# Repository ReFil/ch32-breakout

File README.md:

# ch32-breakout
 A Small ch32 breakout board complete with octagons

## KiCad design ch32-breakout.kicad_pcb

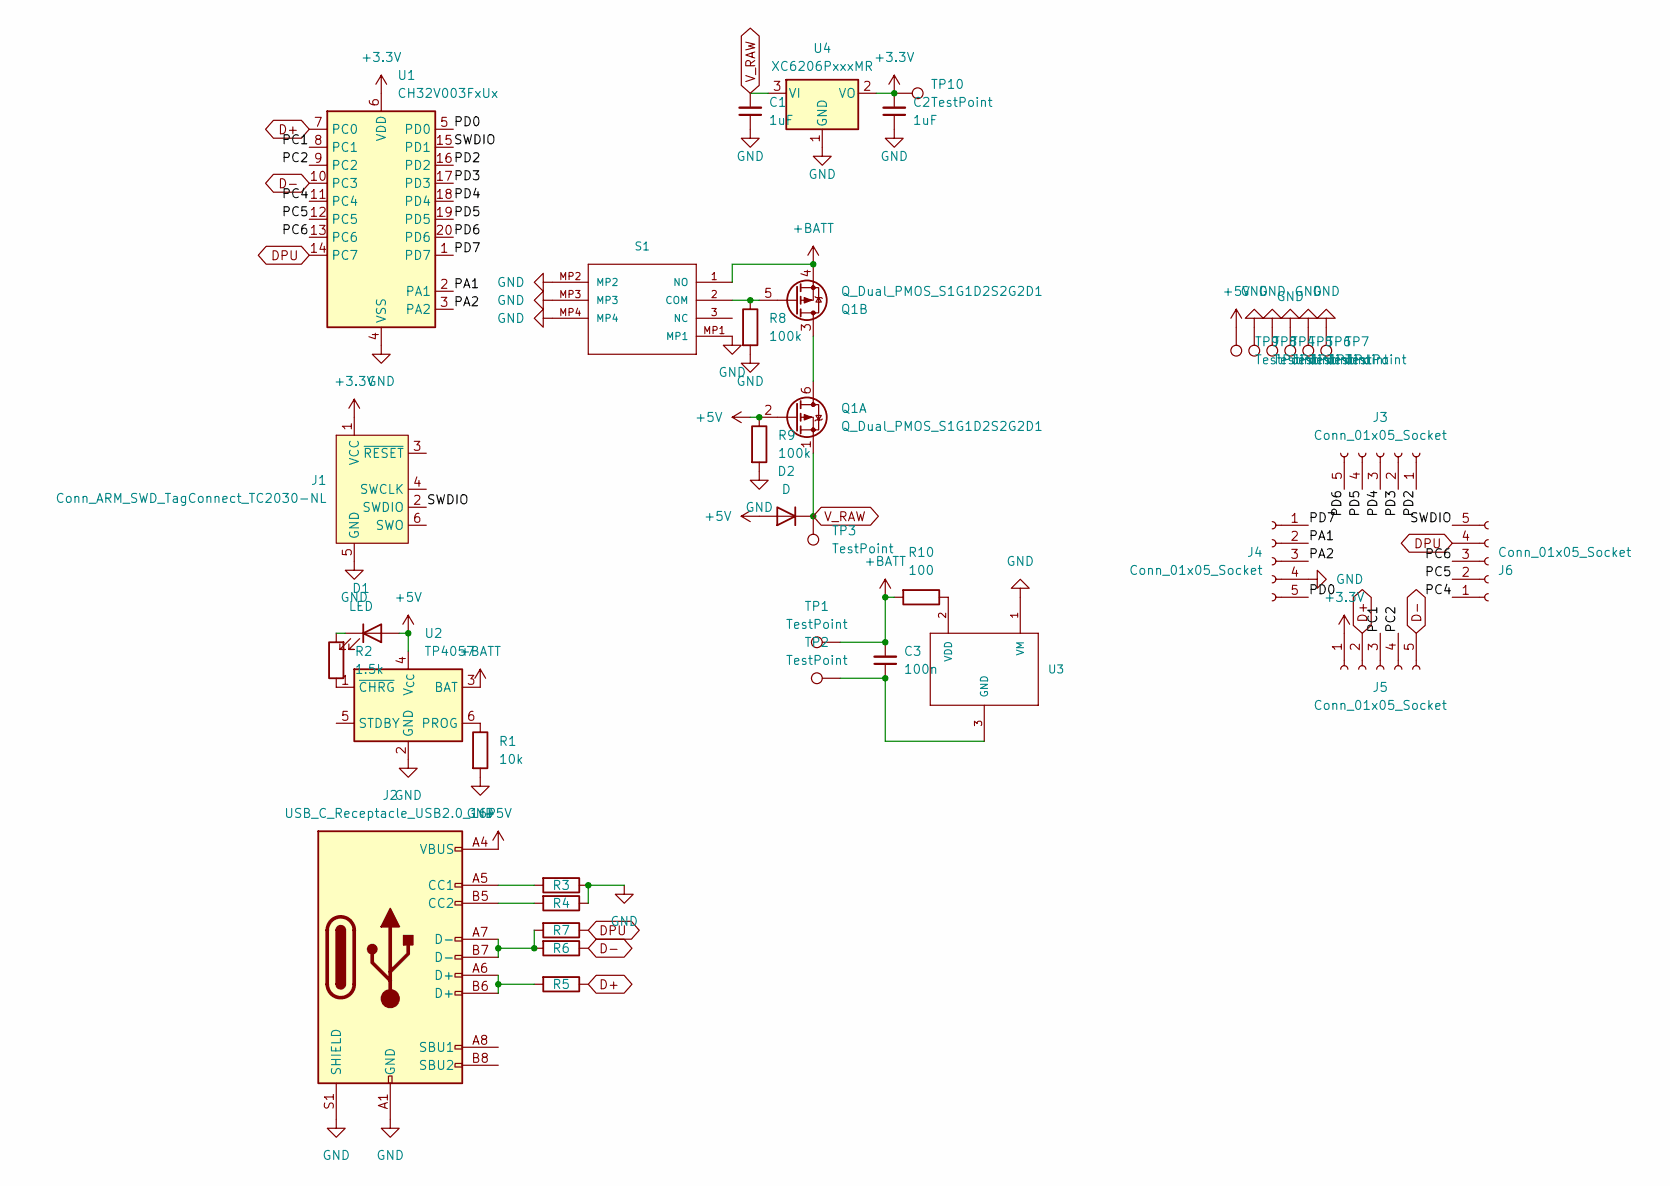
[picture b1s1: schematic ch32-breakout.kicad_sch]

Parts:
C1, C2: 1uF; C_0402_1005Metric; LCSC Part Number C2169363
C3: 100n; C_0402_1005Metric; LCSC Part Number C2169363
D1: LED; LED_0402_1005Metric; LCSC Part C5336761
D2: D; D_0603_1608Metric; LCSC Part C3758192
J1: Conn_ARM_SWD_TagConnect_TC2030-NL; Tag-Connect_TC2030-IDC-NL_2x03_P1.27mm_Vertical
J2: USB_C_Receptacle_USB2.0_16P; USB_C_Receptacle_XKB_U262-16XN-4BVC11; LCSC Part C319148
J3, J4, J5, J6: Conn_01x05_Socket; PinHeader_1x05_P1.27mm_Vertical_SMD_Pin1Left
Q1: Q_Dual_PMOS_S1G1D2S2G2D1; SOT-563; LCSC Part C504144
R1: 10k; R_0402_1005Metric; LCSC Part C60490
R2, R7: 1.5k; R_0402_1005Metric; LCSC Part C2929900
R3, R4: 5.1k; R_0402_1005Metric; LCSC Part C103086
R5, R6: 47; R_0402_1005Metric; LCSC Part C137973
R8, R9: 100k; R_0402_1005Metric; LCSC Part C2906883
R10: 100; R_0402_1005Metric; LCSC Part C106232
S1: SK-3296S-01-L1; SK3296S01L1; LCSC Part C319020
TP1, TP2, TP3, TP4, TP5, TP6, TP7, TP8, TP9: TestPoint; TestPoint_Pad_1.5x1.5mm
TP10: TestPoint; TestPoint_Pad_D1.0mm
U1: CH32V003FxUx; QFN-20-1EP_3x3mm_P0.4mm_EP1.65x1.65mm; LCSC Part C5299908
U2: TP4057; TSOT-23-6; LCSC Part C12044
U3: XB3303ASOT23; SOT-23; LCSC Part C154937
U4: XC6206PxxxMR; SOT-23-3; LCSC Part C5252899

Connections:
+3.3V: C2.2, J1.1 (VCC), J5.1, TP10.1, U1.6 (VDD), U4.2 (VO)
+5V: D1.2 (A), D2.2 (A), J2.A4 (VBUS), J2.A9 (VBUS), J2.B4 (VBUS), J2.B9 (VBUS), Q1.2 (G), R9.1, TP9.1, U2.4 (V_{CC})
+BATT: C3.2, Q1.4 (S), R10.2, S1.1 (NO), TP1.1, U2.3 (BAT)
/PA1: J4.2, U1.2 (PA1)
/PA2: J4.3, U1.3 (PA2)
/PC1: J5.3, U1.8 (PC1)
/PC2: J5.4, U1.9 (PC2)
/PC4: J6.1, U1.11 (PC4)
/PC5: J6.2, U1.12 (PC5)
/PC6: J6.3, U1.13 (PC6)
/PD0: J4.5, U1.5 (PD0)
/PD2: J3.1, U1.16 (PD2)
/PD3: J3.2, U1.17 (PD3)
/PD4: J3.3, U1.18 (PD4)
/PD5: J3.4, U1.19 (PD5)
/PD6: J3.5, U1.20 (PD6)
/PD7: J4.1, U1.1 (PD7)
/SWDIO: J1.2 (SWDIO), J6.5, U1.15 (PD1)
D+: J5.2, R5.1, U1.7 (PC0)
D-: J5.5, R6.1, U1.10 (PC3)
DPU: J6.4, R7.1, U1.14 (PC7)
GND: C1.1, C2.1, J1.5 (GND), J2.A1 (GND), J2.A12 (GND), J2.B1 (GND), J2.B12 (GND), J2.S1 (SHIELD), J4.4, R1.2, R3.1, R4.1, R8.2, R9.2, S1.MP1, S1.MP2, S1.MP3, S1.MP4, TP4.1, TP5.1, TP6.1, TP7.1, TP8.1, U1.4 (VSS), U1.21 (VSS), U2.2 (GND), U3.1 (VM), U4.1 (GND)
unnamed: D1.1 (K), R2.2
unnamed: J2.A5 (CC1), R3.2
unnamed: J2.B5 (CC2), R4.2
unnamed: J2.A6 (D+), J2.B6 (D+), R5.2
unnamed: J2.A7 (D-), J2.B7 (D-), R6.2, R7.2
unnamed: Q1.3 (D), Q1.6 (D)
unnamed: Q1.5 (G), R8.1, S1.2 (COM)
unnamed: R1.1, U2.6 (PROG)
unnamed: R2.1, U2.1 (~CHRG)
unnamed: C3.1, TP2.1, U3.3 (GND)
unnamed: R10.1, U3.2 (VDD)
V_RAW: C1.2, D2.1 (K), Q1.1 (S), TP3.1, U4.3 (VI)

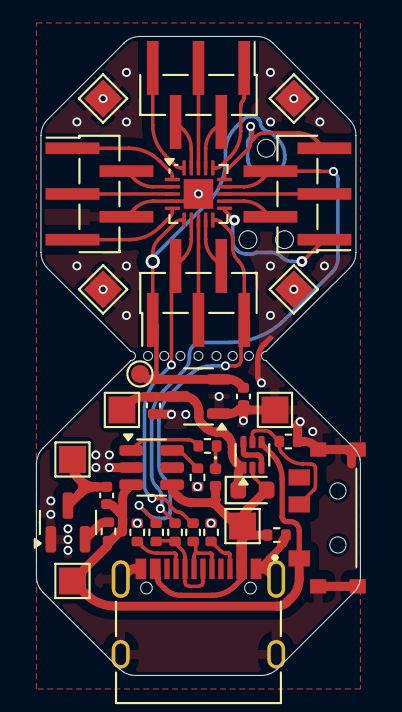
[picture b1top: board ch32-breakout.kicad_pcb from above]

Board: 2 copper layers, 18.0 x 35.5 mm, 37 parts (1 on the bottom side), 34 nets.

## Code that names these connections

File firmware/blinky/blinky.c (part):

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 * 05-29-2023 recallmenot adapted from Timer1 to Timer2
 *
 * Usage: 
 * Connect LEDs between PD3 and GND, PD4 and GND, PC1 and GND, and PC7 and GND
 * Observe activity on PD3 and PD4, then activity on PC1 and PC7, and back
 *
 * Nutshell:
 * 1. Ensure you're providing a clock to the AFIO peripheral! Save yourself an 
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
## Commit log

2025-06-08 Board complete pre rounding
2025-06-12 Bpard finished it's kibot time
2025-06-15 export gerbers
2025-08-02 Initial blinky example
2025-08-06 Workign PWM and interrupt
2025-08-08 It's working pretty good now
2025-08-11 Add additional effects and fix updown
